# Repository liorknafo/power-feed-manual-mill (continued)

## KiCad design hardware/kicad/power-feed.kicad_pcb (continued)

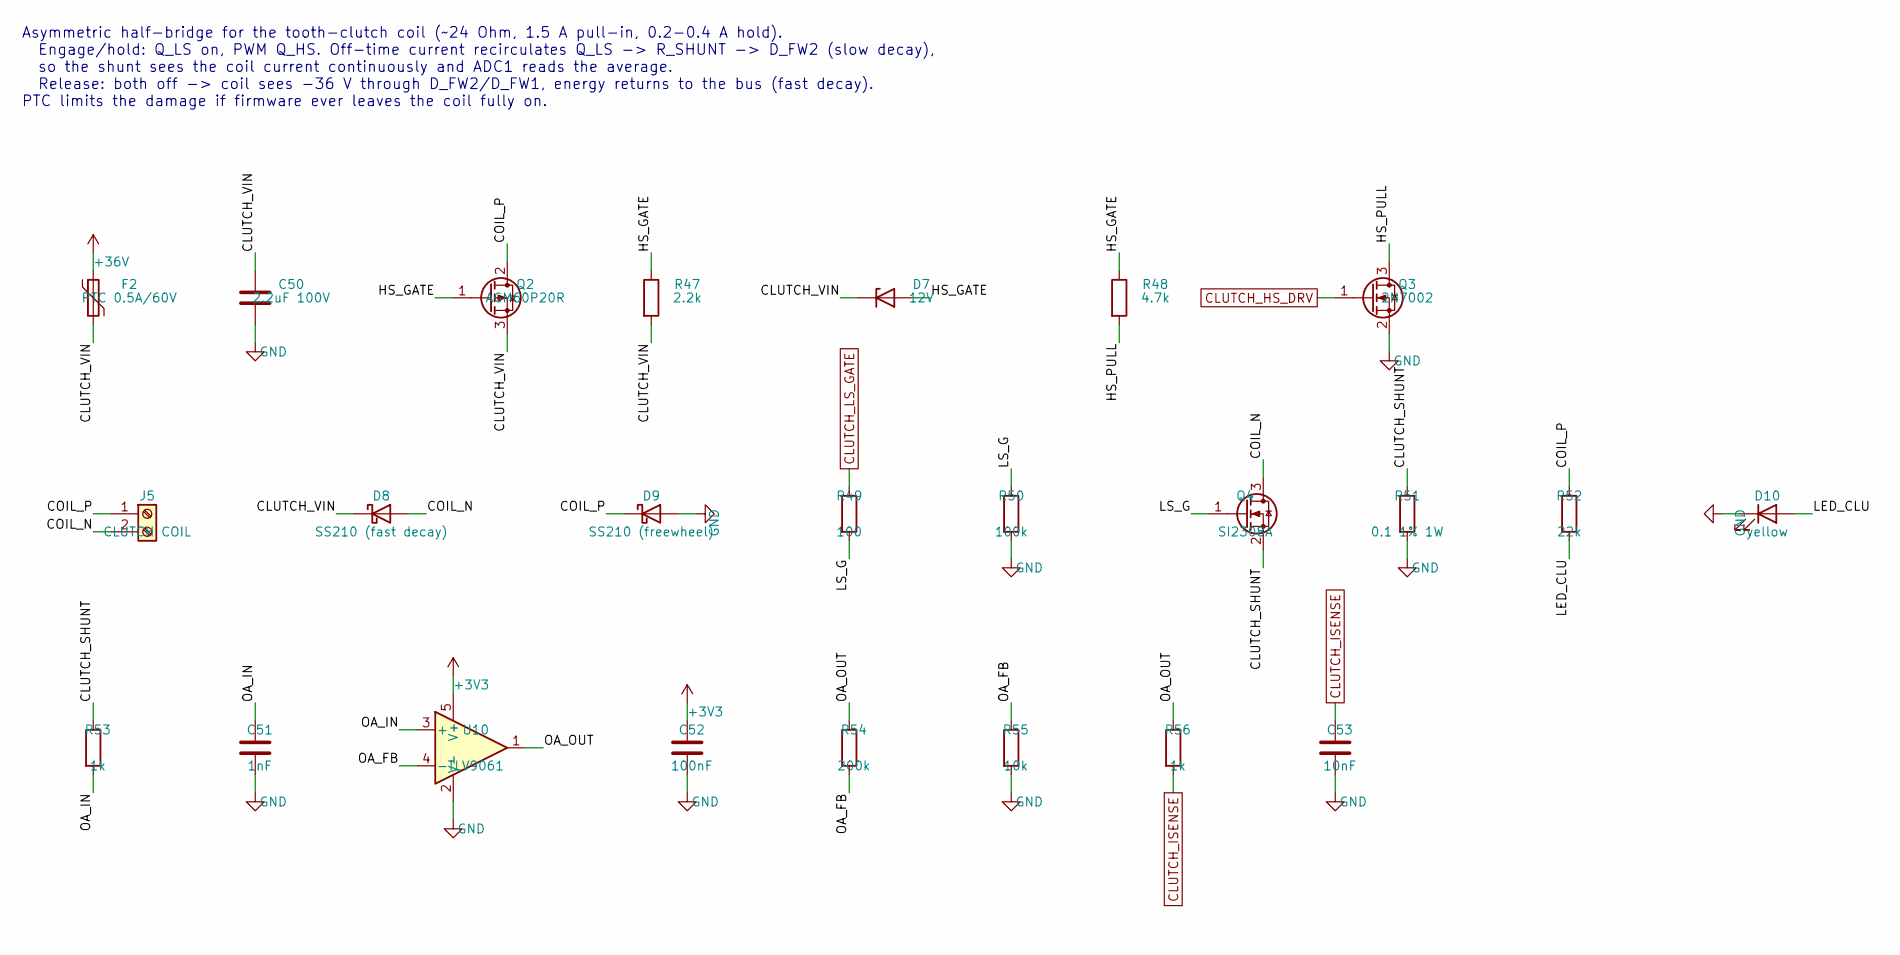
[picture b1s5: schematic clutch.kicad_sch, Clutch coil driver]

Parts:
C50: 2.2uF 100V; C_1210_3225Metric; MPN Murata GRM32ER72A225KA35L; LCSC C86054
C51: 1nF; C_0603_1608Metric; MPN Samsung CL10B102KB8NNNC; LCSC C1588
C52: 100nF; C_0603_1608Metric; MPN Yageo CC0603KRX7R9BB104; LCSC C14663
C53: 10nF; C_0603_1608Metric; MPN FH 0603B103K500NT; LCSC C57112
D7: 12V; D_SOD-123; MPN onsemi MMSZ5242BT1G; LCSC C82050
D8: SS210 (fast decay); D_SMA; MPN SS210; LCSC C14996
D9: SS210 (freewheel); D_SMA; MPN SS210; LCSC C14996
D10: yellow; LED_0603_1608Metric; MPN XINGLIGHT XL-1608UYC-06; LCSC C965802
F2: PTC 0.5A/60V; Fuse_2920_7451Metric; MPN Littelfuse 2920L050DR (0.5 A hold, 1 A 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; LCSC C207082
J5: CLUTCH COIL; PhoenixContact_MSTBA_2,5_2-G-5,08_1x02_P5.08mm_Horizontal; MPN KF2EDGR-5.08-2P (+ plug KF2EDGK-5.08-2P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; LCSC C441204
Q2: AGM60P20R; SOT-223-3_TabPin2; MPN AGM60P20R; LCSC C6719402
Q3: 2N7002; SOT-23; MPN 2N7002; LCSC C8545
Q4: SI2308A; SOT-23; MPN UMW SI2308A; LCSC C347491
R47: 2.2k; R_0603_1608Metric; MPN UNI-ROYAL 0603WAF2201T5E; LCSC C4190
R48: 4.7k; R_1206_3216Metric; MPN UNI-ROYAL 1206W4F4701T5E; LCSC C17936
R49: 100; R_0603_1608Metric; MPN UNI-ROYAL 0603WAF1000T5E; LCSC C22775
R50: 100k; R_0603_1608Metric; MPN UNI-ROYAL 0603WAF1003T5E; LCSC C25803
R51: 0.1 1% 1W; R_1206_3216Metric; MPN FOJAN FRM121WFR100TM; LCSC C7467250
R52: 22k; R_0603_1608Metric; MPN UNI-ROYAL 0603WAF2202T5E; LCSC C31850
R53, R56: 1k; R_0603_1608Metric; MPN UNI-ROYAL 0603WAF1001T5E; LCSC C21190
R54: 200k; R_0603_1608Metric; MPN UNI-ROYAL 0603WAF2003T5E; LCSC C25811
R55: 10k; R_0603_1608Metric; MPN UNI-ROYAL 0603WAF1002T5E; LCSC C25804
U10: TLV9061; SOT-23-5; MPN TLV9061IDBVR; LCSC C398358

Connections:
+3V3: C52.1, U10.5 (V+); also elsewhere on the board
+36V: F2.1; also elsewhere on the board
/Clutch coil driver/CLUTCH_SHUNT: Q4.2 (S), R51.1, R53.1
/Clutch coil driver/CLUTCH_VIN: C50.1, D7.1 (K), D8.1 (K), F2.2, Q2.3 (S), R47.2
/Clutch coil driver/COIL_N: D8.2 (A), J5.2, Q4.3 (D)
/Clutch coil driver/COIL_P: D9.1 (K), J5.1, Q2.2 (D), R52.1
/Clutch coil driver/HS_GATE: D7.2 (A), Q2.1 (G), R47.1, R48.1
/Clutch coil driver/HS_PULL: Q3.3 (D), R48.2
/Clutch coil driver/LED_CLU: D10.2 (A), R52.2
/Clutch coil driver/LS_G: Q4.1 (G), R49.2, R50.1
/Clutch coil driver/OA_FB: R54.2, R55.1, U10.4 (-)
/Clutch coil driver/OA_IN: C51.1, R53.2, U10.3 (+)
/Clutch coil driver/OA_OUT: R54.1, R56.1, U10.1
CLUTCH_HS_DRV: Q3.1 (G); also elsewhere on the board
CLUTCH_ISENSE: C53.1, R56.2; also elsewhere on the board
CLUTCH_LS_GATE: R49.1; also elsewhere on the board
GND: C50.2, C51.2, C52.2, C53.2, D9.2 (A), D10.1 (K), Q3.2 (S), R50.2, R51.2, R55.2, U10.2 (V-); also elsewhere on the board

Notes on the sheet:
Asymmetric half-bridge for the tooth-clutch coil (~24 Ohm, 1.5 A pull-in, 0.2-0.4 A hold). Engage/hold: Q_LS on, PWM Q_HS. Off-time current recirculates Q_LS -> R_SHUNT -> D_FW2 (slow decay), so the shunt sees the coil current continuously and ADC1 reads the average. Release: both off -> coil sees 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

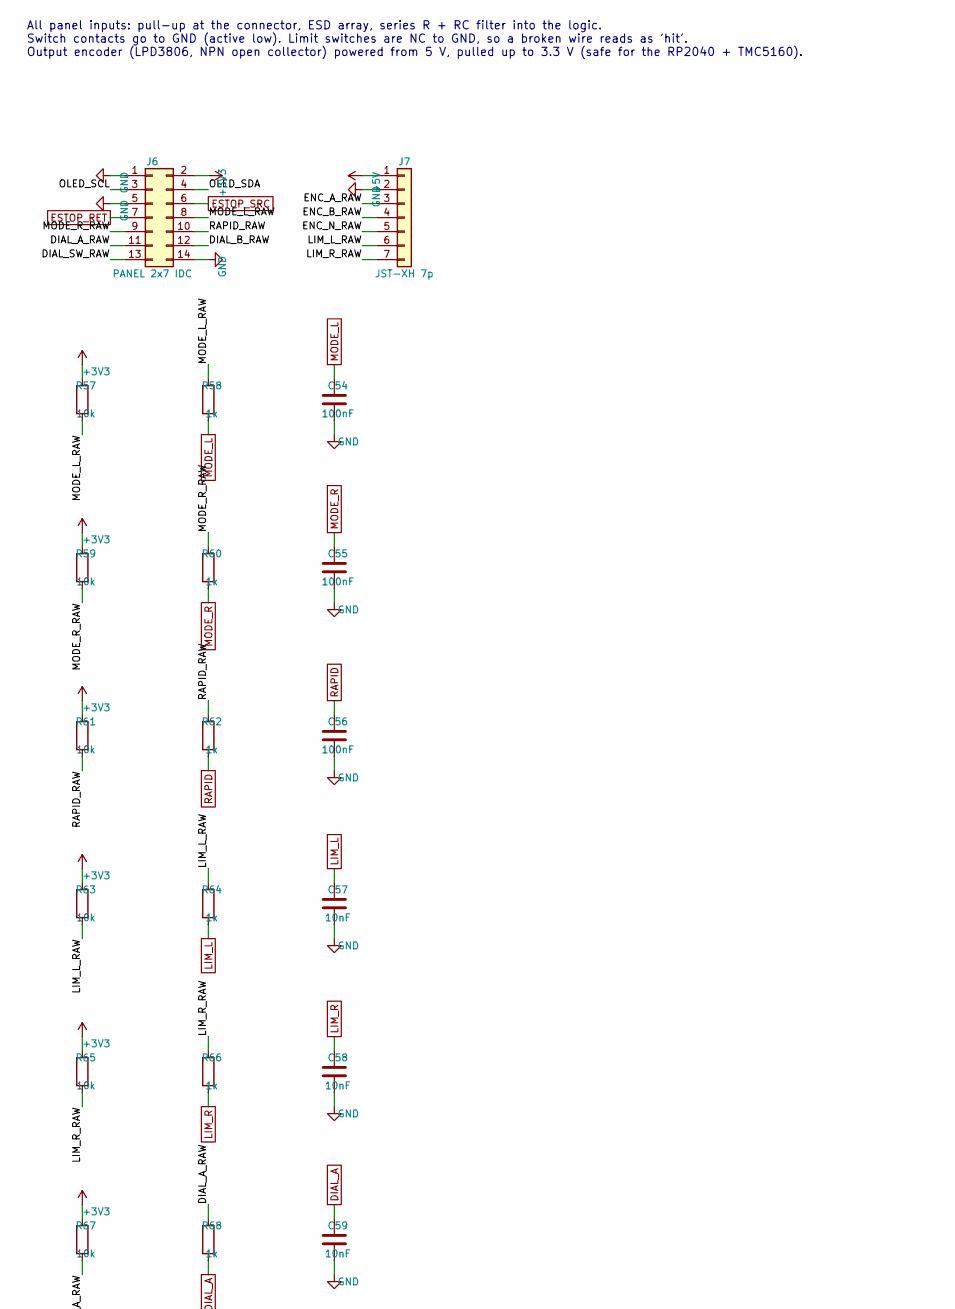
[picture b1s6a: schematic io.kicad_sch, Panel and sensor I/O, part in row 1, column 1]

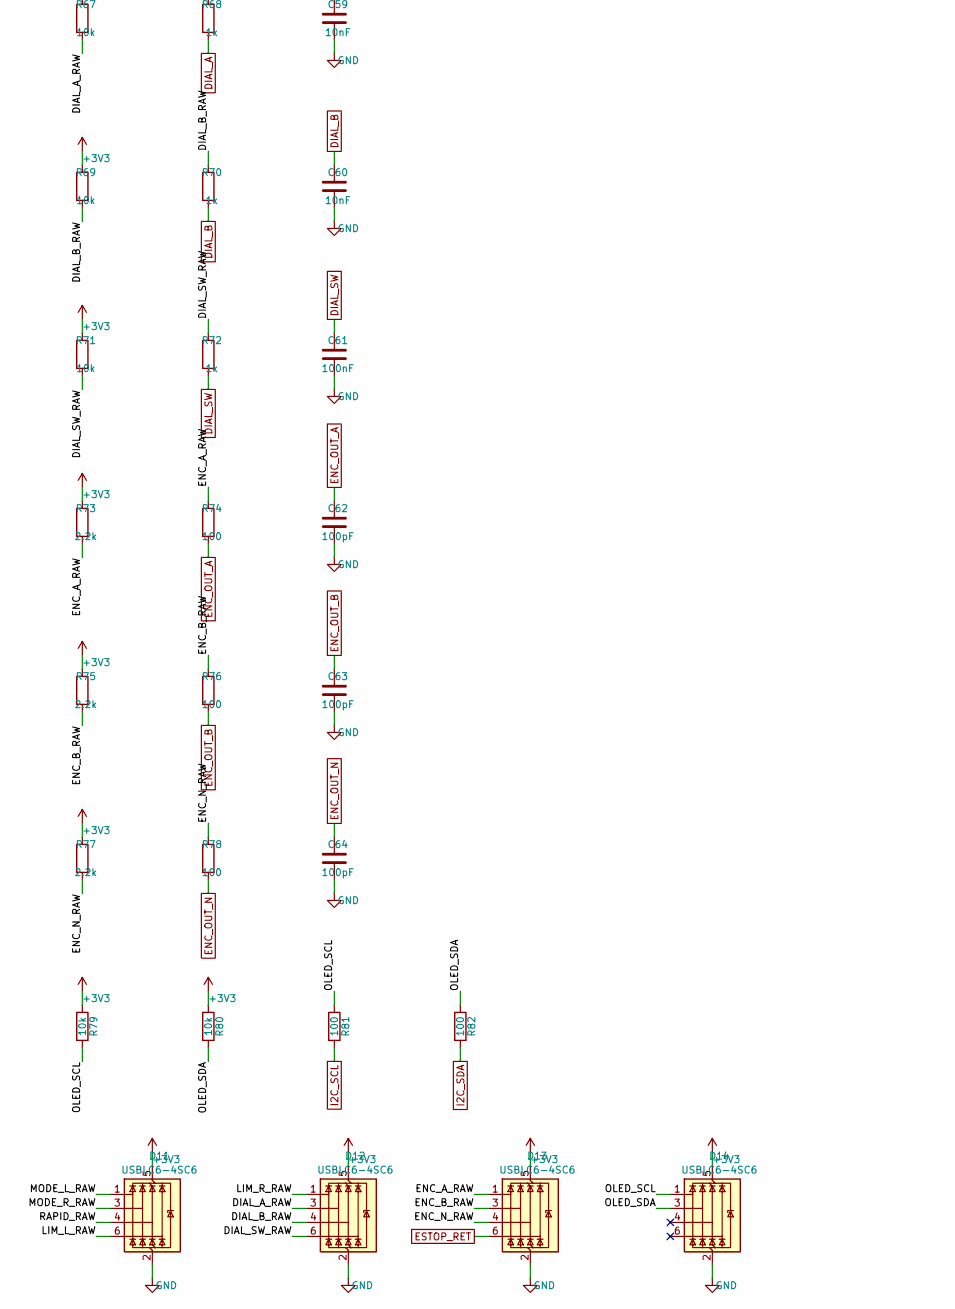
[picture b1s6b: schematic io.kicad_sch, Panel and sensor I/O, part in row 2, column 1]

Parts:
C54, C55, C56, C61: 100nF; C_0603_1608Metric; MPN Yageo CC0603KRX7R9BB104; LCSC C14663
C57, C58, C59, C60: 10nF; C_0603_1608Metric; MPN FH 0603B103K500NT; LCSC C57112
C62, C63, C64: 100pF; C_0603_1608Metric; MPN Samsung CL10C101JB8NNNC; LCSC C14858
D11, D12, D13, D14: USBLC6-4SC6; SOT-23-6; MPN USBLC6-4SC6; LCSC C111212
J6: PANEL 2x7 IDC; IDC-Header_2x07_P2.54mm_Vertical; MPN ZHOURI DC3-2.54-14PAS (2x7 shrouded box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; LCSC C2977595
J7: JST-XH 7p; JST_XH_B7B-XH-A_1x07_P2.50mm_Vertical; MPN JST B7B-XH-A(LF)(SN); LCSC C144398
R57, R59, R61, R63, R65, R67, R69, R71, R79, R80: 10k; R_0603_1608Metric; MPN UNI-ROYAL 0603WAF1002T5E; LCSC C25804
R58, R60, R62, R64, R66, R68, R70, R72: 1k; R_0603_1608Metric; MPN UNI-ROYAL 0603WAF1001T5E; LCSC C21190
R73, R75, R77: 2.2k; R_0603_1608Metric; MPN UNI-ROYAL 0603WAF2201T5E; LCSC C4190
R74, R76, R78, R81, R82: 100; R_0603_1608Metric; MPN UNI-ROYAL 0603WAF1000T5E; LCSC C22775

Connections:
+3V3: D11.5 (VBUS), D12.5 (VBUS), D13.5 (VBUS), D14.5 (VBUS), J6.2, R57.1, R59.1, R61.1, R63.1, R65.1, R67.1, R69.1, R71.1, R73.1, R75.1, R77.1, R79.1, R80.1; also elsewhere on the board
+5V: J7.1; also elsewhere on the board
/Panel and sensor I/O/DIAL_A_RAW: D12.3 (I/O2), J6.11, R67.2, R68.1
/Panel and sensor I/O/DIAL_B_RAW: D12.4 (I/O3), J6.12, R69.2, R70.1
/Panel and sensor I/O/DIAL_SW_RAW: D12.6 (I/O4), J6.13, R71.2, R72.1
/Panel and sensor I/O/ENC_A_RAW: D13.1 (I/O1), J7.3, R73.2, R74.1
/Panel and sensor I/O/ENC_B_RAW: D13.3 (I/O2), J7.4, R75.2, R76.1
/Panel and sensor I/O/ENC_N_RAW: D13.4 (I/O3), J7.5, R77.2, R78.1
/Panel and sensor I/O/LIM_L_RAW: D11.6 (I/O4), J7.6, R63.2, R64.1
/Panel and sensor I/O/LIM_R_RAW: D12.1 (I/O1), J7.7, R65.2, R66.1
/Panel and sensor I/O/MODE_L_RAW: D11.1 (I/O1), J6.8, R57.2, R58.1
/Panel and sensor I/O/MODE_R_RAW: D11.3 (I/O2), J6.9, R59.2, R60.1
/Panel and sensor I/O/OLED_SCL: D14.1 (I/O1), J6.3, R79.2, R81.1
/Panel and sensor I/O/OLED_SDA: D14.3 (I/O2), J6.4, R80.2, R82.1
/Panel and sensor I/O/RAPID_RAW: D11.4 (I/O3), J6.10, R61.2, R62.1
DIAL_A: C59.1, R68.2; also elsewhere on the board
DIAL_B: C60.1, R70.2; also elsewhere on the board
DIAL_SW: C61.1, R72.2; also elsewhere on the board
ENC_OUT_A: C62.1, R74.2; also elsewhere on the board
ENC_OUT_B: C63.1, R76.2; also elsewhere on the board
ENC_OUT_N: C64.1, R78.2; also elsewhere on the board
ESTOP_RET: D13.6 (I/O4), J6.7; also elsewhere on the board
ESTOP_SRC: J6.6; also elsewhere on the board
GND: C54.2, C55.2, C56.2, C57.2, C58.2, C59.2, C60.2, C61.2, C62.2, C63.2, C64.2, D11.2 (GND), D12.2 (GND), D13.2 (GND), D14.2 (GND), J6.1, J6.5, J6.14, J7.2; also elsewhere on the board
I2C_SCL: R81.2; also elsewhere on the board
I2C_SDA: R82.2; also elsewhere on the board
LIM_L: C57.1, R64.2; also elsewhere on the board
LIM_R: C58.1, R66.2; also elsewhere on the board
MODE_L: C54.1, R58.2; also elsewhere on the board
MODE_R: C55.1, R60.2; also elsewhere on the board
RAPID: C56.1, R62.2; also elsewhere on the board

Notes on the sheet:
All panel inputs: pull-up at the connector, ESD array, series R + RC filter into the logic. Switch contacts go to GND (active low). Limit switches are NC to GND, so a broken wire reads as 'hit'. Output encoder (LPD3806, NPN open collector) powered from 5 V, pulled up to 3.3 V (safe for the RP2040 +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

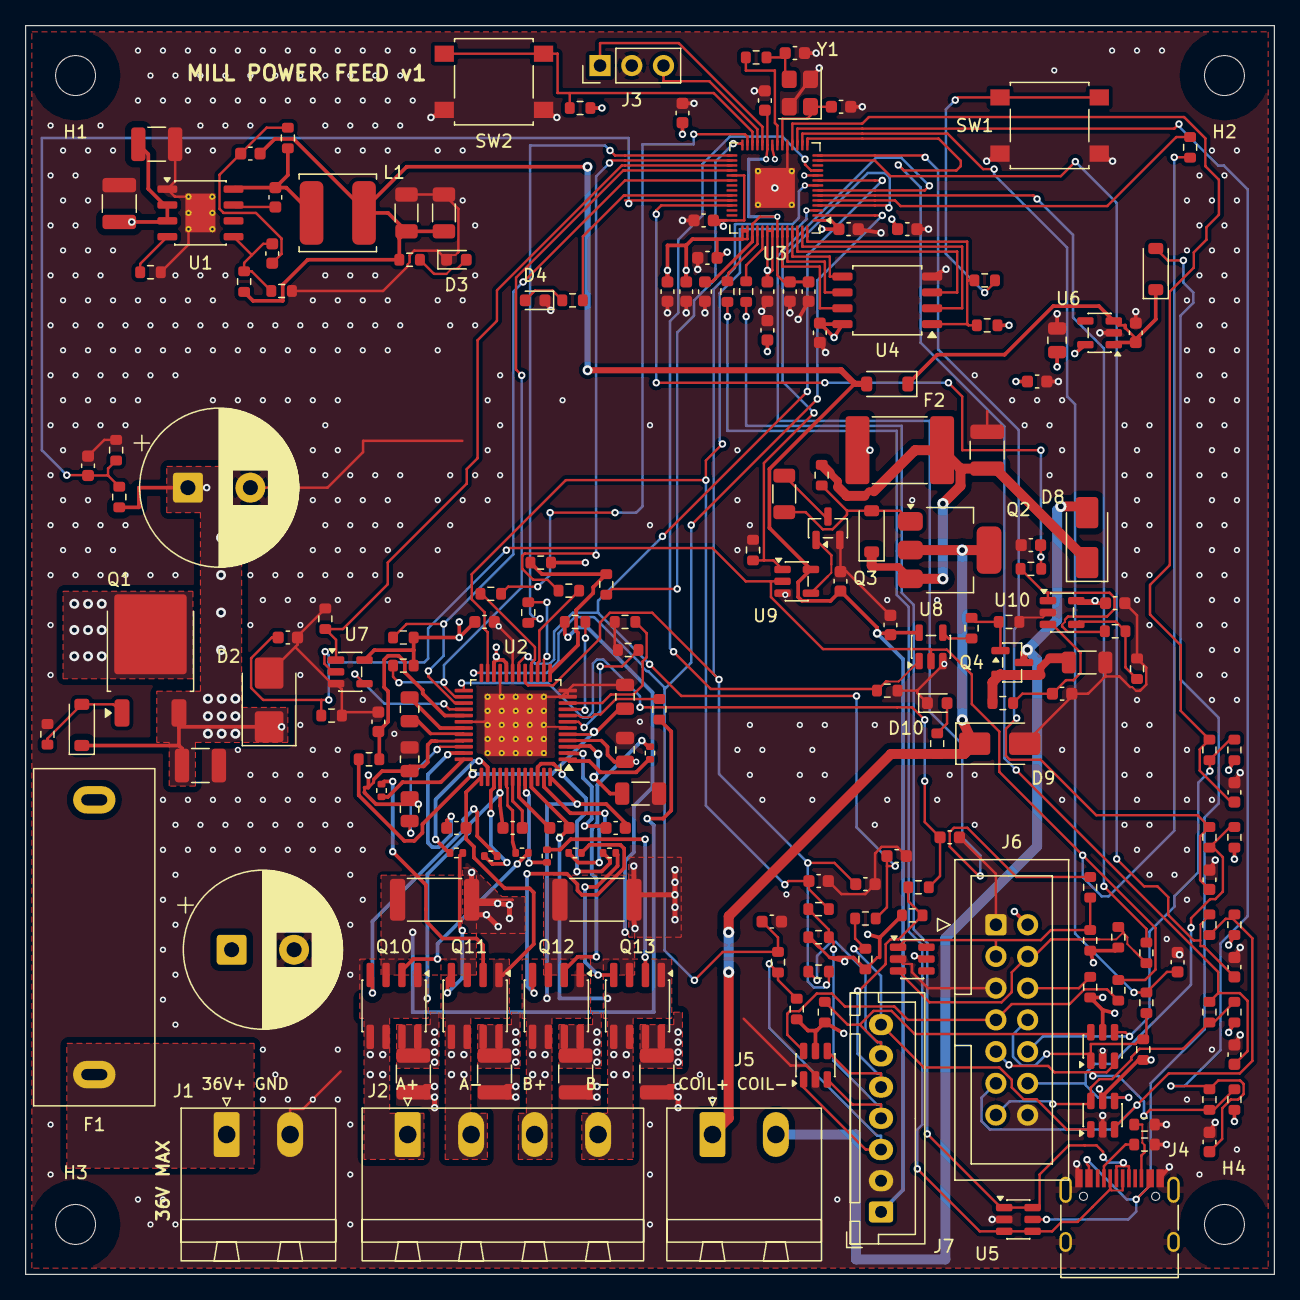
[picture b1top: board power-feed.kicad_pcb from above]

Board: 4 copper layers, 100.0 x 100.0 mm, 195 parts (0 on the bottom side), 132 nets.

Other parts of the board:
H1, H2, H3, H4: M3; MountingHole_3.2mm_M3

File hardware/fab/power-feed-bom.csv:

Comment,Designator,Footprint,LCSC Part #,MPN
2.2nF 50V,C5,C_0603_1608Metric,C1604,FH 0603B222K500NT
3.3nF,C6,C_0603_1608Metric,C1613,Samsung CL10B332KB8NNNC
22nF 100V,C13,C_0805_2012Metric,C107137,Yageo CC0805KRX7R0BB223
470nF,C16,C_0603_1608Metric,C1623,Samsung CL10B474KA8NNNC
10uF 25V,C17,C_1206_3216Metric,C13585,Samsung CL31A106KBHNNNE
1nF,C51,C_0603_1608Metric,C1588,Samsung CL10B102KB8NNNC
470uF 63V,"C1,C27",CP_Radial_D12.5mm_P5.00mm,C407954,Panasonic EEUFR1J471
10nF,"C10,C53,C57,C58,C59,C60",C_0603_1608Metric,C57112,FH 0603B103K500NT
100nF 100V,"C11,C12,C14",C_0805_2012Metric,C28233,Samsung CL21B104KCFNNNE
4.7uF 10V,"C15,C45",C_0805_2012Metric,C1779,Samsung CL21A475KAQNNNE
100nF,"C18,C28,C29,C30,C31,C32,C33,C34,C35,C38,C39,C40,C41,C46,C47,C48,C49,C52,C54,C55,C56,C61",C_0603_1608Metric,C14663,Yageo CC0603KRX7R9BB104
220nF 50V,"C19,C21,C23,C25",C_0603_1608Metric,C64705,Samsung CL10B224KB8NNNC
2.2uF 100V,"C2,C3,C4,C20,C22,C24,C26,C50",C_1210_3225Metric,C86054,Murata GRM32ER72A225KA35L
1uF,"C36,C37,C44",C_0603_1608Metric,C15849,Samsung CL10A105KB8NNNC
15pF,"C42,C43",C_0603_1608Metric,C1644,Samsung CL10C150JB8NNNC
100pF,"C7,C62,C63,C64",C_0603_1608Metric,C14858,Samsung CL10C101JB8NNNC
22uF 10V,"C8,C9",C_1206_3216Metric,C12891,Samsung CL31A226KAHNNNE
15V,D1,D_SOD-123,C129730,onsemi MMSZ5245BT1G
SMBJ36A (TVS),D2,D_SMB,C114001,SMBJ36A
12V,D7,D_SOD-123,C82050,onsemi MMSZ5242BT1G
SS210 (fast decay),D8,D_SMA,C14996,SS210
SS210 (freewheel),D9,D_SMA,C14996,SS210
yellow,D10,LED_0603_1608Metric,C965802,XINGLIGHT XL-1608UYC-06
USBLC6-4SC6,"D11,D12,D13,D14",SOT-23-6,C111212,USBLC6-4SC6
green,"D3,D4",LED_0603_1608Metric,C12624,KENTO KT-0603G
B5819W,"D5,D6",D_SOD-123,C8598,Changjing B5819W SL
5A T 5x20,F1,Fuseholder_XC_BLX-A_5x20mm_P22.00mm,C3131,BLX-A holder + Littelfuse 0215005.MXP (C142718)
PTC 0.5A/60V,F2,Fuse_2920_7451Metric,C207082,"Littelfuse 2920L050DR (0.5 A hold, 1 A trip, 60 V)"
36V IN,J1,"PhoenixContact_MSTBA_2,5_2-G-5,08_1x02_P5.08mm_Horizontal",C441204,KF2EDGR-5.08-2P (+ plug KF2EDGK-5.08-2P C440880)
MOTOR A+ A- B+ B-,J2,"PhoenixContact_MSTBA_2,5_4-G-5,08_1x04_P5.08mm_Horizontal",C441206,KF2EDGR-5.08-4P (+ plug KF2EDGK-5.08-4P C440882)
SWD,J3,PinHeader_1x03_P2.54mm_Vertical,,"2.54 mm 1x3 male header, hand-solder (Debug Probe's JST-to-0.1in cable)"
USB-C,J4,USB_C_Receptacle_HRO_TYPE-C-31-M-12,C165948,HRO TYPE-C-31-M-12
CLUTCH COIL,J5,"PhoenixContact_MSTBA_2,5_2-G-5,08_1x02_P5.08mm_Horizontal",C441204,KF2EDGR-5.08-2P (+ plug KF2EDGK-5.08-2P C440880)
PANEL 2x7 IDC,J6,IDC-Header_2x07_P2.54mm_Vertical,C2977595,ZHOURI DC3-2.54-14PAS (2x7 shrouded box header)
JST-XH 7p,J7,JST_XH_B7B-XH-A_1x07_P2.50mm_Vertical,C144398,JST B7B-XH-A(LF)(SN)
47uH,L1,L_TDK_VLS6045EX_VLS6045AF,C404505,TDK VLS6045EX-470M
SQD50P06-15L,Q1,TO-252-2,C3281500,SQD50P06-15L_GE3
AGM60P20R,Q2,SOT-223-3_TabPin2,C6719402,AGM60P20R
2N7002,Q3,SOT-23,C8545,2N7002
SI2308A,Q4,SOT-23,C347491,UMW SI2308A
CSD88537ND,"Q10,Q11,Q12,Q13",SOIC-8_3.9x4.9mm_P1.27mm,C117439,CSD88537ND
41.2k,R2,R_0603_1608Metric,C2930101,FOJAN FRC0603F4122TS
31.6k,R4,R_0603_1608Metric,C25967,UNI-ROYAL 0603WAF3162T5E
4.7k,R6,R_0603_1608Metric,C23162,UNI-ROYAL 0603WAF4701T5E
7.5k,R8,R_0603_1608Metric,C23234,UNI-ROYAL 0603WAF7501T5E
2.2,R9,R_0603_1608Metric,C22939,UNI-ROYAL 0603WAF220KT5E
330,R43,R_0603_1608Metric,C23138,UNI-ROYAL 0603WAF3300T5E
4.7k,R48,R_1206_3216Metric,C17936,UNI-ROYAL 1206W4F4701T5E
0.1 1% 1W,R51,R_1206_3216Metric,C7467250,FOJAN FRM121WFR100TM
22k,"R1,R52",R_0603_1608Metric,C31850,UNI-ROYAL 0603WAF2202T5E
4.7,"R10,R11,R12,R13,R14,R15,R16,R17",R_0402_1005Metric,C25121,UNI-ROYAL 0402WGF470KTCE
0.05 1% 3W,"R18,R21",R_2512_6332Metric,C346860,CSM2512FT50L0
47,"R19,R20,R22,R23",R_0603_1608Metric,C23182,UNI-ROYAL 0603WAF470JT5E
10k,"R24,R27,R37,R38,R39,R45,R55,R57,R59,R61,R63,R65,R67,R69,R71,R79,R80",R_0603_1608Metric,C25804,UNI-ROYAL 0603WAF1002T5E
1k,"R25,R26,R28,R44,R53,R56,R58,R60,R62,R64,R66,R68,R70,R72",R_0603_1608Metric,C21190,UNI-ROYAL 0603WAF1001T5E
5.1k,"R29,R30",R_0603_1608Metric,C23186,UNI-ROYAL 0603WAF5101T5E
100k,"R3,R7,R40,R41,R42,R46,R50",R_0603_1608Metric,C25803,UNI-ROYAL 0603WAF1003T5E
27,"R31,R32",R_0603_1608Metric,C25190,UNI-ROYAL 0603WAF270JT5E
33,"R33,R34,R35,R36",R_0603_1608Metric,C23140,UNI-ROYAL 0603WAF330JT5E
2.2k,"R47,R73,R75,R77",R_0603_1608Metric,C4190,UNI-ROYAL 0603WAF2201T5E
100,"R49,R74,R76,R78,R81,R82",R_0603_1608Metric,C22775,UNI-ROYAL 0603WAF1000T5E
200k,"R5,R54",R_0603_1608Metric,C25811,UNI-ROYAL 0603WAF2003T5E
BOOTSEL,SW1,SW_SPST_B3S-1000,C2733655,Omron B3S-1000
RESET,SW2,SW_SPST_B3S-1000,C2733655,Omron B3S-1000
LM5164DDAR,U1,HSOP-8-1EP_3.9x4.9mm_P1.27mm_EP2.41x3.1mm_ThermalVias,C477928,LM5164DDAR
TMC5160A-TA,U2,TQFP-48-1EP_7x7mm_P0.5mm_EP5x5mm_ThermalVias,C516354,
RP2040,U3,QFN-56-1EP_7x7mm_P0.4mm_EP3.2x3.2mm_ThermalVias,C2040,Raspberry Pi RP2040
W25Q128JVS,U4,SOIC-8_5.3x5.3mm_P1.27mm,C113767,Winbond W25Q128JVSIQ (W25Q16 is out of stock; firmware uses the first 2 MB)
USBLC6-2SC6,U5,SOT-23-6,C7519,STMicroelectronics USBLC6-2SC6
AP2112K-3.3,U6,SOT-23-5,C51118,Diodes AP2112K-3.3TRG1
74LVC1G00,U7,SOT-23-5,C7826,SN74LVC1G00DBVR
TLV9061,U10,SOT-23-5,C398358,TLV9061IDBVR
74AHCT1G08,"U8,U9",SOT-23-5,C113521,SN74AHCT1G08DBVR
12MHz,Y1,Crystal_SMD_3225-4Pin_3.2x2.5mm,C20625731,"Abracon ABM8-272-T3 (12 MHz, CL 10 pF, ESR 50R; RPi-approved)"

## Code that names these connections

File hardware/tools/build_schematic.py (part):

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        "20": "XIN", "21": "XOUT", "24": "SWCLK", "25": "SWDIO", "26": "RUN",
        "46": "USB_DM", "47": "USB_DP",
        "51": "QSPI_SD3", "52": "QSPI_SCLK", "53": "QSPI_SD0", "54": "QSPI_SD2", "55": "QSPI_SD1", "56": "QSPI_SS",
        "2": "ENC_OUT_A", "3": "ENC_OUT_B", "4": "CLUTCH_HS_PWM", "5": "E_OK_SENSE",          # GPIO0..3
        "6": "I2C_SDA", "7": "I2C_SCL", "8": "LIM_L", "9": "LIM_R", "11": "CLUTCH_LS_EN",    # GPIO4..8
        "13": "DIAL_A", "14": "DIAL_B", "15": "DIAL_SW", "16": "MODE_L", "17": "MODE_R",    # GPIO10..14
        "18": "RAPID", "27": "SPI_MISO", "28": "SPI_CS", "29": "SPI_SCK", "30": "SPI_MOSI",  # GPIO15..19
        "31": "DRV_EN", "32": "TMC_DIAG0", "34": "TMC_DIAG1", "37": "LED_STAT",              # GPIO20..22, 25
        "38": "VM_SENSE", "39": "CLUTCH_ISENSE",                                             # GPIO26/27 = ADC0/1
    })
    s.row(Part("U", "MCU_RaspberryPi:RP2040", "RP2040", QFN56, mcu, props=P("Raspberry Pi RP2040", "C2040")))
    s.row(*[C("100nF", V3, GND) for _ in range(6)], C("100nF", V3, GND), C("100nF", V3, GND),   # IOVDD x6, AVDD, USB_VDD
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
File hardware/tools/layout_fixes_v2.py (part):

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   are boxed in by SRAL, SRBL, LIM_L and the LIM_R / ENC_OUT_A / ENC_OUT_N B.Cu diagonals, and neither hand
   routing nor Freerouting found a corridor back to R18 / R21 pad 2 without rerouting that block.

5. Bridge returns. MOT_A1/MOT_B1/MOT_B2 to U2 pins 40/48/45 attach at the phase pours next to the FET
   source pins instead of at the J2 pins.

6. SNS_A node width: G_HA2 is rerouted and the SNS_A pour outline redrawn, which widens the Q11 pin 3 -> R18
   path from 0.8 mm to 0.85 mm at its one pinch (G_HA2 corner (33.4, 73.1) to G_HA1's via (32.99, 74.75), about
   0.5 mm long; everywhere else >= 1.2 mm). G_HA1's via cannot move further: MOT_A1 and the SNS_A sense line run
   under it on B.Cu and Q10 pin 1 bounds its F.Cu run.

7. 36 V clearance. power-feed.kicad_dru adds a 0.5 mm clearance rule for the 36 V nets (+36V, VIN_*, MOT_*,
   CLUTCH_VIN, COIL_P/N) on the outer layers; pads of the fine-pitch power parts (U1, U2, Q2-Q4) and the drivers'
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    return n


# ------------------------------------------------------------- 6. SNS_A node width at Q11 pin 3 (G_HA2 reroute)

def fix6_sns_a_neck(board):
    """G_HA2 crossed the SNS_A pour diagonally right between Q11 pin 4 and pin 3, pinching the pour to 0.8 mm.
    It now crosses higher (y 73.1) and drops vertically onto pin 2; the pour edge moves to x 36.1."""
    g = TMC + "G_HA2"
    n = remove_track(board, g, F, (32.062, 70.776), (36.635, 75.35)) + remove_track(board, g, F, (36.635, 75.35), (36.635, 76.025))
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    # passes its GND pad at 0.5 mm, and the via sits beyond C12 pad 1 (TMC_HB1's diagonal limits it to 0.5 mm)
    n += move_fp(board, "C12", 48.0, 58.0)
    n += remove_tracks_in(board, "+36V", F, (43.3, 56.9, 49.5, 59.5)) + remove_via(board, "+36V", (46.983, 58.183))
    # (0.23 mm beside the U2 pin 3 TMC_12V escape, as originally routed, then 0.3 mm)
    n += add_track(board, "+36V", F, (43.413, 57.25), (46.1, 57.25), 0.23)
    n += add_path(board, "+36V", F, [(46.1, 57.25), (46.6, 57.75), (46.6, 58.4), (47.15, 58.95), (48.9, 58.95)], 0.3)
    n += add_via(board, "+36V", (48.9, 58.95), 0.5, 0.25)
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
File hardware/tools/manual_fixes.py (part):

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   (85.0, 27.6) inside the +3V3 top region of In2 (y < 28), clear of the Pico VSYS track. The redundant
   via through U6 pad 5 and the two redundant vias through C28 pad 1 (Pico decoupling) are removed.

3. TMC_CA1 (U2 pin 42 -> bootstrap cap C19): pin 40 (MOT_A1) and pin 42 (CA1) feed C19 whose pads were
   on the wrong sides (CA1 pad left, MOT_A1 pad right), so the two nets had to cross; the router gave up
   and left three dangling vias. C19 is rotated 180 deg. Then MOT_A1 goes straight down from pin 40 to
   pad 2, CA1 goes down from pin 42 and jogs right to pad 1, and HA1 (pin 41, between them) runs between
   the two C19 pads down to R10. The old HA1 loop around the right of C19 is removed. Gate/bootstrap
   tracks stay under 7 mm.

4. GND fill islands at D9 and D10 (USBLC6 ESD arrays): pin 2 (GND) sits mid-row with signal tracks on
   all four sides, so the F.Cu pour fragment on the pad is isolated. A 0.5/0.25 mm GND via is placed
   just off the pad end, overlapping the pad, with a short stub. At D9 the MODE_L_RAW track that passes
   under the body is moved up 0.25 mm to make room.

5. Dangling via clean-up: the TMC_LB2 via with nothing on B.Cu is removed.
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
def fix4_gnd_islands(board):
    n = 0
    # D10 pin 2: via just above the pad end, 0.2 mm below the DIAL_B_RAW track at y = 87.05
    n += add_via(board, "GND", (86.25, 87.6), 0.5, 0.25)
    n += add_track(board, "GND", F, (86.25, 88.388), (86.25, 87.6), 0.25)
    # D9 pin 2: move MODE_L_RAW (runs under the body at y = 81.805) up to y = 81.55, then via above pad 2
    m = IO + "MODE_L_RAW"
    n += remove_track(board, m, F, (85.841, 81.805), (85.3, 82.346))
    n += remove_track(board, m, F, (88.87, 81.805), (85.841, 81.805))
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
